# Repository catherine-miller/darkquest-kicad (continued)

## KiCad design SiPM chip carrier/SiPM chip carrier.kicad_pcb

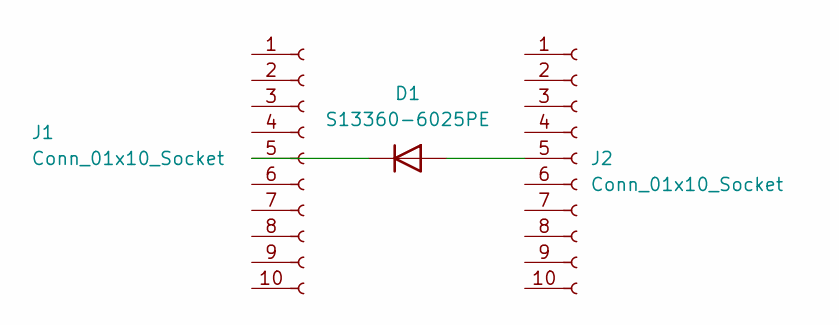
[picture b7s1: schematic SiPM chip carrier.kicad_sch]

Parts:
D1: S13360-6025PE; S13360-6025PE_surfacemount
J1, J2: Conn_01x10_Socket; PinHeader_1x10_P2.54mm_Vertical

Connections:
unnamed: D1.2 (A), J2.5
unnamed: D1.3 (K), J1.5

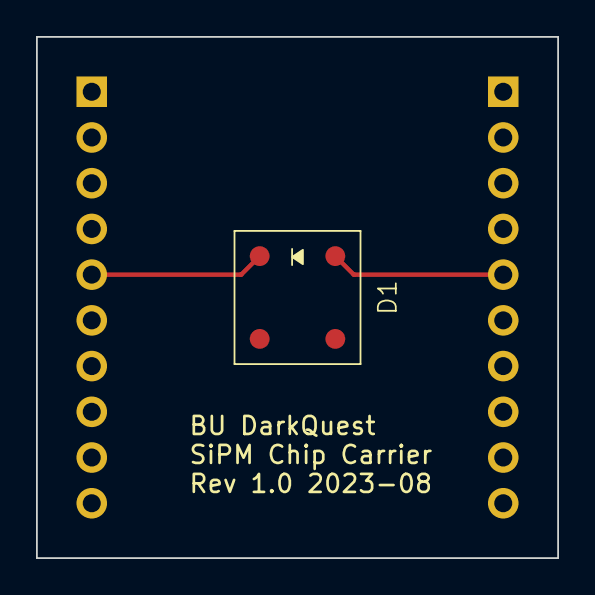
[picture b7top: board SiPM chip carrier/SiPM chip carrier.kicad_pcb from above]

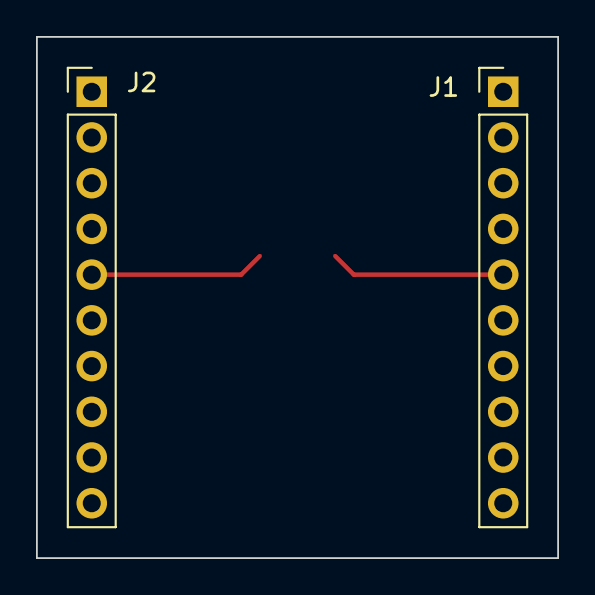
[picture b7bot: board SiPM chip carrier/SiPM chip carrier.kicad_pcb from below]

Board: 2 copper layers, 29.0 x 29.0 mm, 3 parts (2 on the bottom side), 2 nets.

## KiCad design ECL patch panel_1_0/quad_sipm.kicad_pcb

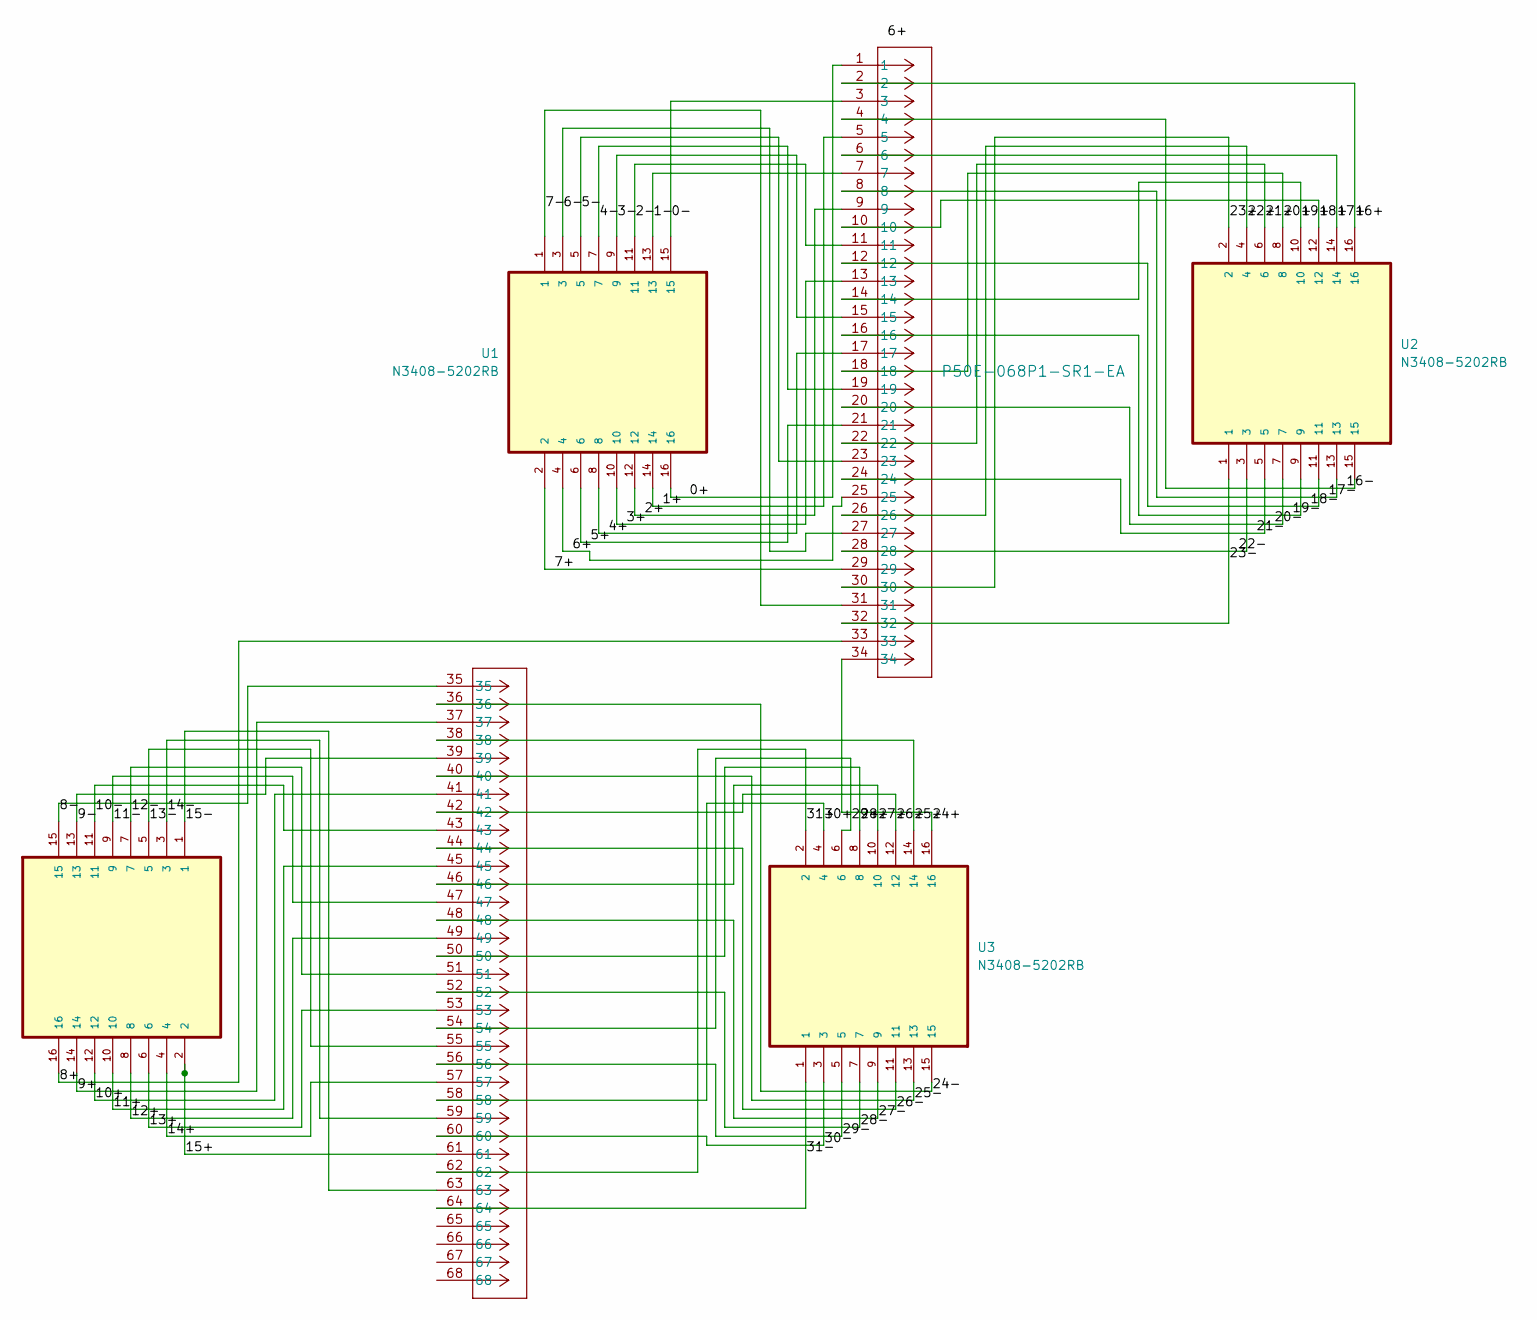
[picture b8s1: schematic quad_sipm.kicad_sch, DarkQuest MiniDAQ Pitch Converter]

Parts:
J1: P50E-068P1-SR1-EA; CONN_P50E-068P1-SR1-EA_3MM
U1, U2, U3, U4: N3408-5202RB; 3M_N3408-5202RB; MPN N3408-5202RB

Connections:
/0+: J1.1, U1.16
/0-: J1.3, U1.15
/1+: J1.5, U1.14
/1-: J1.7, U1.13
/2+: J1.9, U1.12
/2-: J1.11, U1.11
/3+: J1.13, U1.10
/3-: J1.15, U1.9
/4+: J1.17, U1.8
/4-: J1.19, U1.7
/5+: J1.21, U1.6
/5-: J1.23, U1.5
/6+: J1.25, U1.4
/6-: J1.27, U1.3
/7+: J1.29, U1.2
/7-: J1.31, U1.1
/8+: J1.33, U4.16
/8-: J1.35, U4.15
/9+: J1.37, U4.14
/9-: J1.39, U4.13
/10+: J1.41, U4.12
/10-: J1.43, U4.11
/11+: J1.45, U4.10
/11-: J1.47, U4.9
/12+: J1.49, U4.8
/12-: J1.51, U4.7
/13+: J1.53, U4.6
/13-: J1.55, U4.5
/14+: J1.57, U4.4
/14-: J1.59, U4.3
/15+: J1.61, U4.2
/15-: J1.63, U4.1
/16+: J1.2, U2.16
/16-: J1.4, U2.15
/17+: J1.6, U2.14
/17-: J1.8, U2.13
/18+: J1.10, U2.12
/18-: J1.12, U2.11
/19+: J1.14, U2.10
/19-: J1.16, U2.9
/20+: J1.18, U2.8
/20-: J1.20, U2.7
/21+: J1.22, U2.6
/21-: J1.24, U2.5
/22+: J1.26, U2.4
/22-: J1.28, U2.3
/23+: J1.30, U2.2
/23-: J1.32, U2.1
/24+: J1.34, U3.16
/24-: J1.36, U3.15
/25+: J1.38, U3.14
/25-: J1.40, U3.13
/26+: J1.42, U3.12
/26-: J1.44, U3.11
/27+: J1.46, U3.10
/27-: J1.48, U3.9
/28+: J1.50, U3.8
/28-: J1.52, U3.7
/29+: J1.54, U3.6
/29-: J1.56, U3.5
/30+: J1.58, U3.4
/30-: J1.60, U3.3
/31+: J1.62, U3.2
/31-: J1.64, U3.1

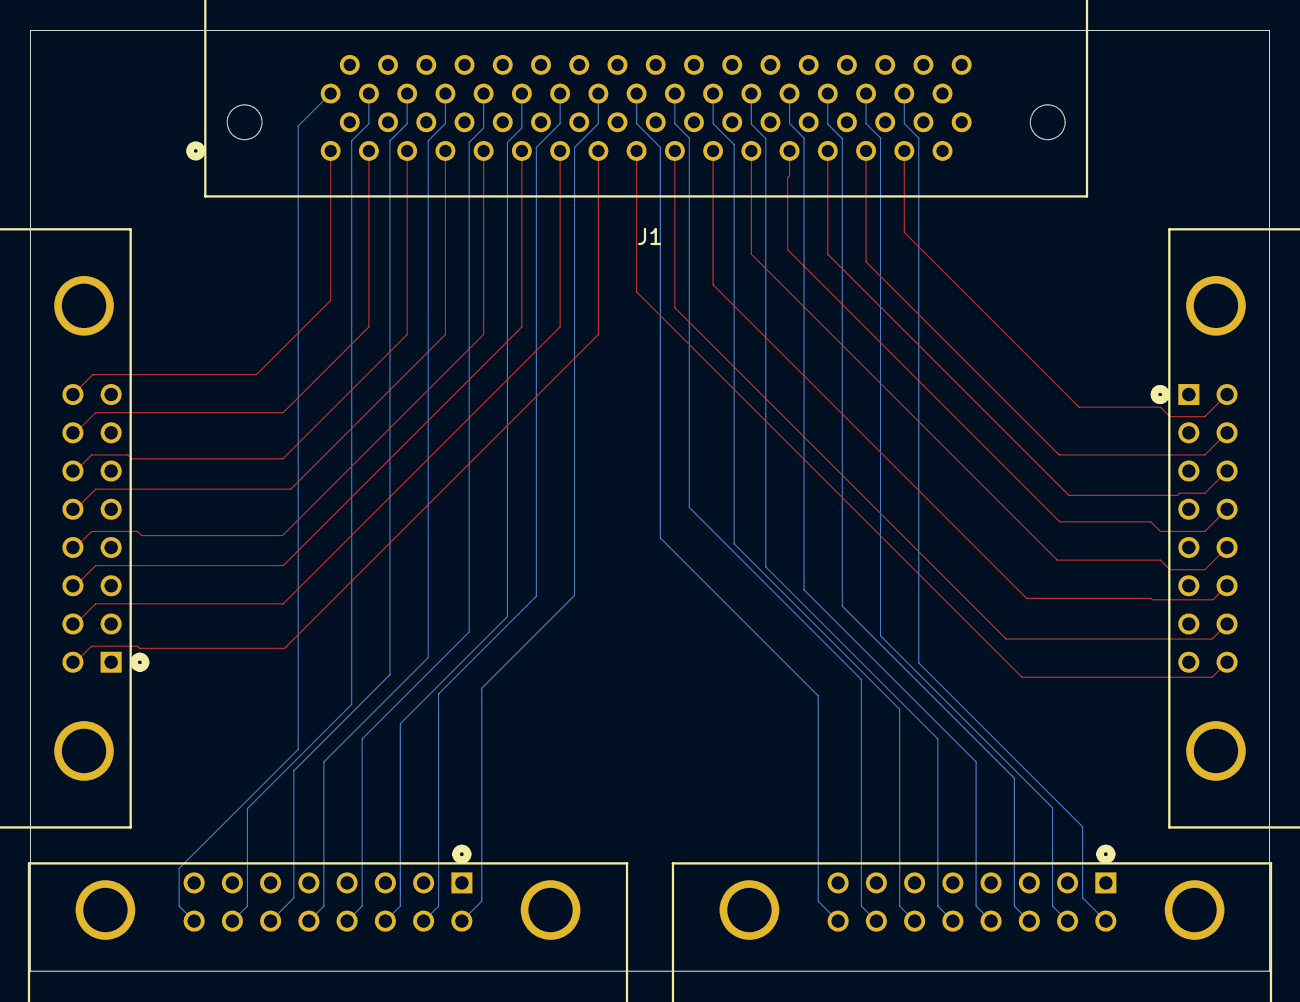
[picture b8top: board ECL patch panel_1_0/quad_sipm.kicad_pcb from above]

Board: 4 copper layers, 82.3 x 62.5 mm, 5 parts (0 on the bottom side), 64 nets.

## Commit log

2023-09-18 initial commit#
2024-01-03 added chip carrier rev 2.0 for new SiPM model
2024-05-09 added Rev 8.1: attenuator switch
